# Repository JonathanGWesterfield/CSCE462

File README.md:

# CSCE 462

Repo to store all lab assignments and eventually the project code for this class

# Wiki Page for this repository can be found here:
[AutoSpiel Wiki Page](https://github.com/JonathanGWesterfield/CSCE462/wiki/Project-Outline "AutoSpiel Wiki Page")

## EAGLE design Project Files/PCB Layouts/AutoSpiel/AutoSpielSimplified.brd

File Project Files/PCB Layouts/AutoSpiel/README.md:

# Important Info
* The schematic is called "AutoSpielSimplified.sch" 
    * This was the final attempt
    * WARNING: this schematic was made without looking at the pinout for the Nu32. There were a couple of corrections that had to be made when building the AutoSpiel (jumping wires across the circuit board)
    * It is highly advised to modify the designs in order to match the Nu32 more closely (the 30 pin connectors)
* The final board layout file is called "AutoSpiel v1.2a"
    * The other files are just different versions and attempts
    * This board had a ground plane in order to dissapate heat
    * Was better than having a single ground trace
* CAM jobs must be done using the FEDC guidlines 
    * Instructions can be found in the FEDC Guidelines folder
    * CAM job file can be found in the FEDC Guidelines folder

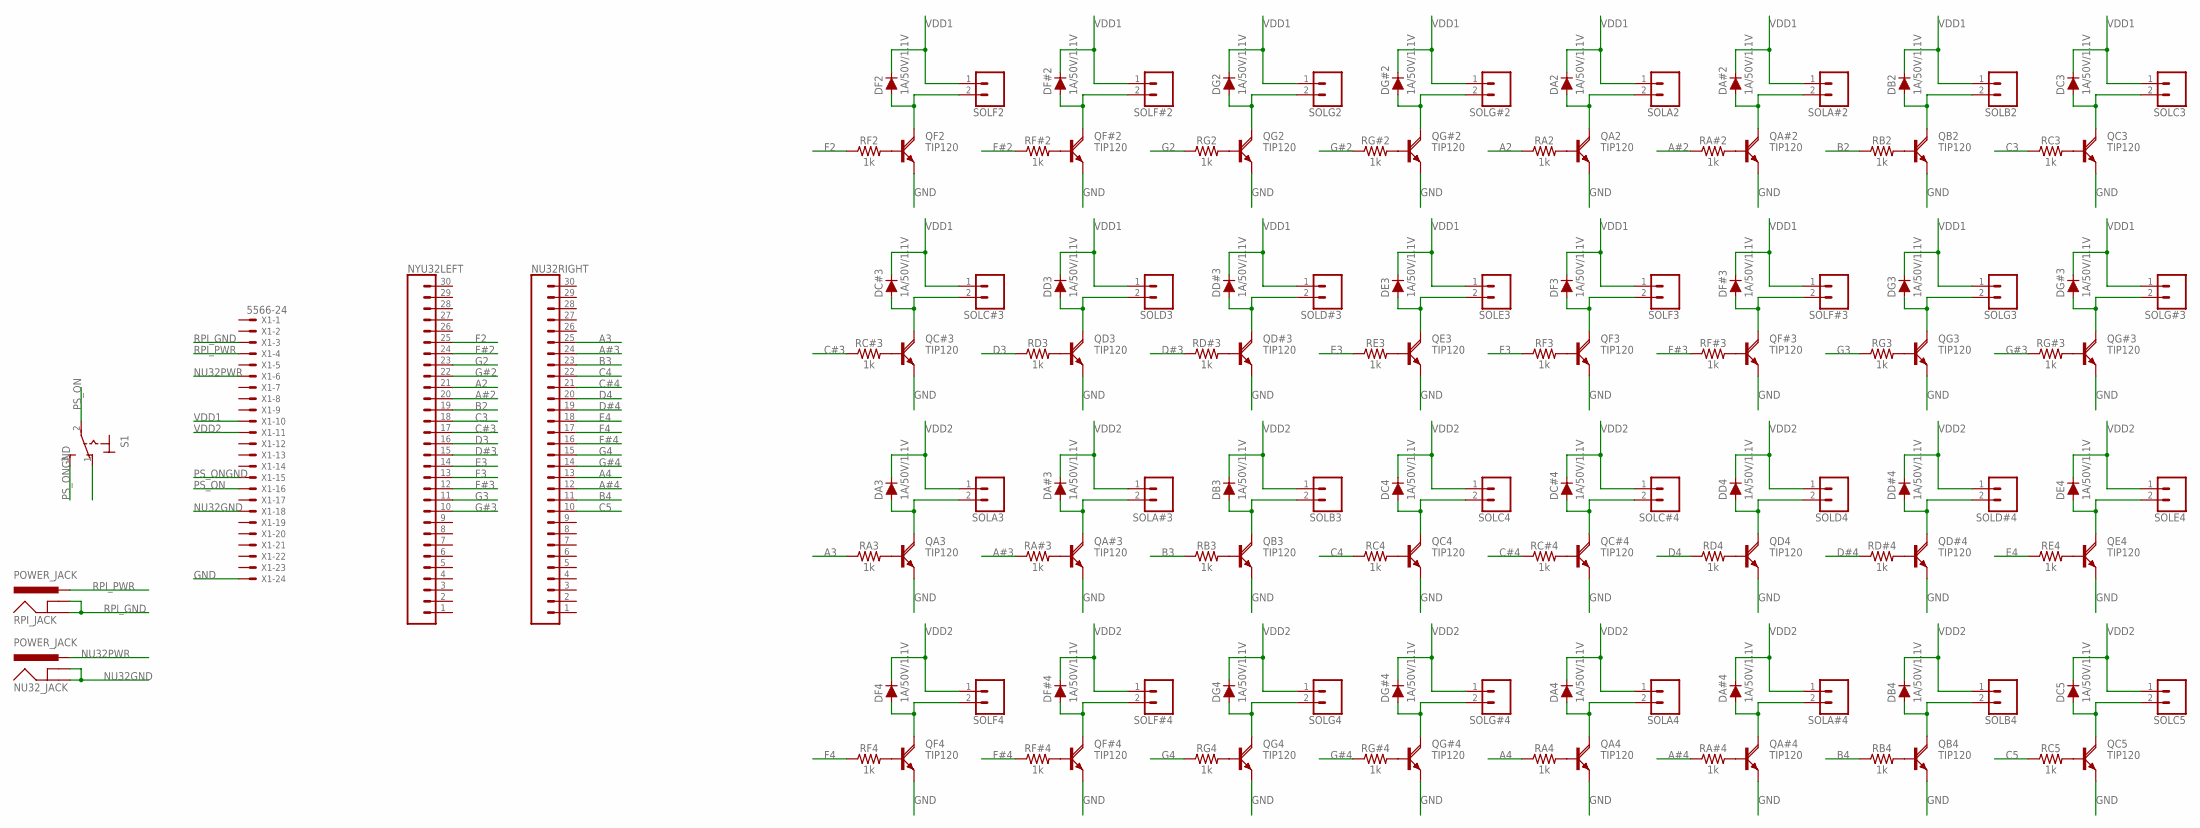
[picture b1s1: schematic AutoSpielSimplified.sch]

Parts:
DA2, DA3, DA4: 1A/50V/1.1V; DIODE-1N4001
DA#2, DA#3, DA#4: 1A/50V/1.1V; DIODE-1N4001
DB2, DB3, DB4: 1A/50V/1.1V; DIODE-1N4001
DC3, DC4, DC5: 1A/50V/1.1V; DIODE-1N4001
DC#3, DC#4: 1A/50V/1.1V; DIODE-1N4001
DD3, DD4: 1A/50V/1.1V; DIODE-1N4001
DD#3, DD#4: 1A/50V/1.1V; DIODE-1N4001
DE3, DE4: 1A/50V/1.1V; DIODE-1N4001
DF2, DF3, DF4: 1A/50V/1.1V; DIODE-1N4001
DF#2, DF#3, DF#4: 1A/50V/1.1V; DIODE-1N4001
DG2, DG3, DG4: 1A/50V/1.1V; DIODE-1N4001
DG#2, DG#3, DG#4: 1A/50V/1.1V; DIODE-1N4001
NU32RIGHT: CONN_30; 1X30
NU32_JACK: POWER_JACK; POWER_JACK_PTH
NYU32LEFT: CONN_30; 1X30
QA2, QA3, QA4: TIP120; TO220AH
QA#2, QA#3, QA#4: TIP120; TO220AH
QB2, QB3, QB4: TIP120; TO220AH
QC3, QC4, QC5: TIP120; TO220AH
QC#3, QC#4: TIP120; TO220AH
QD3, QD4: TIP120; TO220AH
QD#3, QD#4: TIP120; TO220AH
QE3, QE4: TIP120; TO220AH
QF2, QF3, QF4: TIP120; TO220AH
QF#2, QF#3, QF#4: TIP120; TO220AH
QG2, QG3, QG4: TIP120; TO220AH
QG#2, QG#3, QG#4: TIP120; TO220AH
RA2, RA3, RA4: 1k; AXIAL-0.3
RA#2, RA#3, RA#4: 1k; AXIAL-0.3
RB2, RB3, RB4: 1k; AXIAL-0.3
RC3, RC4, RC5: 1k; AXIAL-0.3
RC#3, RC#4: 1k; AXIAL-0.3
RD3, RD4: 1k; AXIAL-0.3
RD#3, RD#4: 1k; AXIAL-0.3
RE3, RE4: 1k; AXIAL-0.3
RF2, RF3, RF4: 1k; AXIAL-0.3
RF#2, RF#3, RF#4: 1k; AXIAL-0.3
RG2, RG3, RG4: 1k; AXIAL-0.3
RG#2, RG#3, RG#4: 1k; AXIAL-0.3
RPI_JACK: POWER_JACK; POWER_JACK_PTH
S1: M9040P
SOLA2, SOLA3, SOLA4: CONN_02PTH4; 1X02_XTRA_BIG
SOLA#2, SOLA#3, SOLA#4: CONN_02PTH4; 1X02_XTRA_BIG
SOLB2, SOLB3, SOLB4: CONN_02PTH4; 1X02_XTRA_BIG
SOLC3, SOLC4, SOLC5: CONN_02PTH4; 1X02_XTRA_BIG
SOLC#3, SOLC#4: CONN_02PTH4; 1X02_XTRA_BIG
SOLD3, SOLD4: CONN_02PTH4; 1X02_XTRA_BIG
SOLD#3, SOLD#4: CONN_02PTH4; 1X02_XTRA_BIG
SOLE3, SOLE4: CONN_02PTH4; 1X02_XTRA_BIG
SOLF2, SOLF3, SOLF4: CONN_02PTH4; 1X02_XTRA_BIG
SOLF#2, SOLF#3, SOLF#4: CONN_02PTH4; 1X02_XTRA_BIG
SOLG2, SOLG3, SOLG4: CONN_02PTH4; 1X02_XTRA_BIG
SOLG#2, SOLG#3, SOLG#4: CONN_02PTH4; 1X02_XTRA_BIG
X1: 5566-24

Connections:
A2: NYU32LEFT.21, RA2.P$1 (1)
A3: NU32RIGHT.25, RA3.P$1 (1)
A4: NU32RIGHT.13, RA4.P$1 (1)
A#2: NYU32LEFT.20, RA#2.P$1 (1)
A#3: NU32RIGHT.24, RA#3.P$1 (1)
A#4: NU32RIGHT.12, RA#4.P$1 (1)
B2: NYU32LEFT.19, RB2.P$1 (1)
B3: NU32RIGHT.23, RB3.P$1 (1)
B4: NU32RIGHT.11, RB4.P$1 (1)
C3: NYU32LEFT.18, RC3.P$1 (1)
C4: NU32RIGHT.22, RC4.P$1 (1)
C5: NU32RIGHT.10, RC5.P$1 (1)
C#3: NYU32LEFT.17, RC#3.P$1 (1)
C#4: NU32RIGHT.21, RC#4.P$1 (1)
D3: NYU32LEFT.16, RD3.P$1 (1)
D4: NU32RIGHT.20, RD4.P$1 (1)
D#3: NYU32LEFT.15, RD#3.P$1 (1)
D#4: NU32RIGHT.19, RD#4.P$1 (1)
E3: NYU32LEFT.14, RE3.P$1 (1)
E4: NU32RIGHT.18, RE4.P$1 (1)
F2: NYU32LEFT.25, RF2.P$1 (1)
F3: NYU32LEFT.13, RF3.P$1 (1)
F4: NU32RIGHT.17, RF4.P$1 (1)
F#2: NYU32LEFT.24, RF#2.P$1 (1)
F#3: NYU32LEFT.12, RF#3.P$1 (1)
F#4: NU32RIGHT.16, RF#4.P$1 (1)
G2: NYU32LEFT.23, RG2.P$1 (1)
G3: NYU32LEFT.11, RG3.P$1 (1)
G4: NU32RIGHT.15, RG4.P$1 (1)
G#2: NYU32LEFT.22, RG#2.P$1 (1)
G#3: NYU32LEFT.10, RG#3.P$1 (1)
G#4: NU32RIGHT.14, RG#4.P$1 (1)
GND: QA2.E, QA3.E, QA4.E, QA#2.E, QA#3.E, QA#4.E, QB2.E, QB3.E, QB4.E, QC3.E, QC4.E, QC5.E, QC#3.E, QC#4.E, QD3.E, QD4.E, QD#3.E, QD#4.E, QE3.E, QE4.E, QF2.E, QF3.E, QF4.E, QF#2.E, QF#3.E, QF#4.E, QG2.E, QG3.E, QG4.E, QG#2.E, QG#3.E, QG#4.E, X1.24
unnamed: QF2.B, RF2.P$2 (2)
unnamed: QC#3.B, RC#3.P$2 (2)
unnamed: DF2.A, QF2.C, SOLF2.2
unnamed: QF#2.B, RF#2.P$2 (2)
unnamed: DF#2.A, QF#2.C, SOLF#2.2
unnamed: DC#3.A, QC#3.C, SOLC#3.2
unnamed: QG2.B, RG2.P$2 (2)
unnamed: DG2.A, QG2.C, SOLG2.2
unnamed: QD3.B, RD3.P$2 (2)
unnamed: QG#2.B, RG#2.P$2 (2)
unnamed: DG#2.A, QG#2.C, SOLG#2.2
unnamed: DD3.A, QD3.C, SOLD3.2
unnamed: QA2.B, RA2.P$2 (2)
unnamed: DA2.A, QA2.C, SOLA2.2
unnamed: QD#3.B, RD#3.P$2 (2)
unnamed: QA#2.B, RA#2.P$2 (2)
unnamed: DA#2.A, QA#2.C, SOLA#2.2
unnamed: DD#3.A, QD#3.C, SOLD#3.2
unnamed: QB2.B, RB2.P$2 (2)
unnamed: DB2.A, QB2.C, SOLB2.2
unnamed: QE3.B, RE3.P$2 (2)
unnamed: QC3.B, RC3.P$2 (2)
unnamed: DC3.A, QC3.C, SOLC3.2
unnamed: DE3.A, QE3.C, SOLE3.2
unnamed: QA3.B, RA3.P$2 (2)
unnamed: DA3.A, QA3.C, SOLA3.2
unnamed: QF3.B, RF3.P$2 (2)
unnamed: DF3.A, QF3.C, SOLF3.2
unnamed: QF#3.B, RF#3.P$2 (2)
unnamed: DF#3.A, QF#3.C, SOLF#3.2
unnamed: QG3.B, RG3.P$2 (2)
unnamed: DG3.A, QG3.C, SOLG3.2
unnamed: QG#3.B, RG#3.P$2 (2)
unnamed: DG#3.A, QG#3.C, SOLG#3.2
unnamed: QF4.B, RF4.P$2 (2)
unnamed: DF4.A, QF4.C, SOLF4.2
unnamed: QF#4.B, RF#4.P$2 (2)
unnamed: DF#4.A, QF#4.C, SOLF#4.2
unnamed: QG4.B, RG4.P$2 (2)
unnamed: DG4.A, QG4.C, SOLG4.2
unnamed: QG#4.B, RG#4.P$2 (2)
unnamed: DG#4.A, QG#4.C, SOLG#4.2
unnamed: QA4.B, RA4.P$2 (2)
unnamed: DA4.A, QA4.C, SOLA4.2
unnamed: QA#4.B, RA#4.P$2 (2)
unnamed: DA#4.A, QA#4.C, SOLA#4.2
unnamed: QB4.B, RB4.P$2 (2)
unnamed: DB4.A, QB4.C, SOLB4.2
unnamed: QC5.B, RC5.P$2 (2)
unnamed: DC5.A, QC5.C, SOLC5.2
unnamed: QA#3.B, RA#3.P$2 (2)
unnamed: DA#3.A, QA#3.C, SOLA#3.2
unnamed: QB3.B, RB3.P$2 (2)
unnamed: DB3.A, QB3.C, SOLB3.2
unnamed: QC4.B, RC4.P$2 (2)
unnamed: DC4.A, QC4.C, SOLC4.2
unnamed: QC#4.B, RC#4.P$2 (2)
unnamed: DC#4.A, QC#4.C, SOLC#4.2
unnamed: QD4.B, RD4.P$2 (2)
unnamed: DD4.A, QD4.C, SOLD4.2
unnamed: QD#4.B, RD#4.P$2 (2)
unnamed: DD#4.A, QD#4.C, SOLD#4.2
unnamed: QE4.B, RE4.P$2 (2)
unnamed: DE4.A, QE4.C, SOLE4.2
NU32GND: NU32_JACK.GND, NU32_JACK.GNDBREAK, X1.18
NU32PWR: NU32_JACK.PWR, X1.6
PS_ON: S1.2, X1.16
PS_ONGND: S1.3 (S), X1.15
RPI_GND: RPI_JACK.GND, RPI_JACK.GNDBREAK, X1.3
RPI_PWR: RPI_JACK.PWR, X1.4
VDD1: DA2.C, DA#2.C, DB2.C, DC3.C, DC#3.C, DD3.C, DD#3.C, DE3.C, DF2.C, DF3.C, DF#2.C, DF#3.C, DG2.C, DG3.C, DG#2.C, DG#3.C, SOLA2.1, SOLA#2.1, SOLB2.1, SOLC3.1, SOLC#3.1, SOLD3.1, SOLD#3.1, SOLE3.1, SOLF2.1, SOLF3.1, SOLF#2.1, SOLF#3.1, SOLG2.1, SOLG3.1, SOLG#2.1, SOLG#3.1, X1.10
VDD2: DA3.C, DA4.C, DA#3.C, DA#4.C, DB3.C, DB4.C, DC4.C, DC5.C, DC#4.C, DD4.C, DD#4.C, DE4.C, DF4.C, DF#4.C, DG4.C, DG#4.C, SOLA3.1, SOLA4.1, SOLA#3.1, SOLA#4.1, SOLB3.1, SOLB4.1, SOLC4.1, SOLC5.1, SOLC#4.1, SOLD4.1, SOLD#4.1, SOLE4.1, SOLF4.1, SOLF#4.1, SOLG4.1, SOLG#4.1, X1.11

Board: 2 copper layers, 134 parts (0 on the bottom side), 105 nets, no tracks yet.

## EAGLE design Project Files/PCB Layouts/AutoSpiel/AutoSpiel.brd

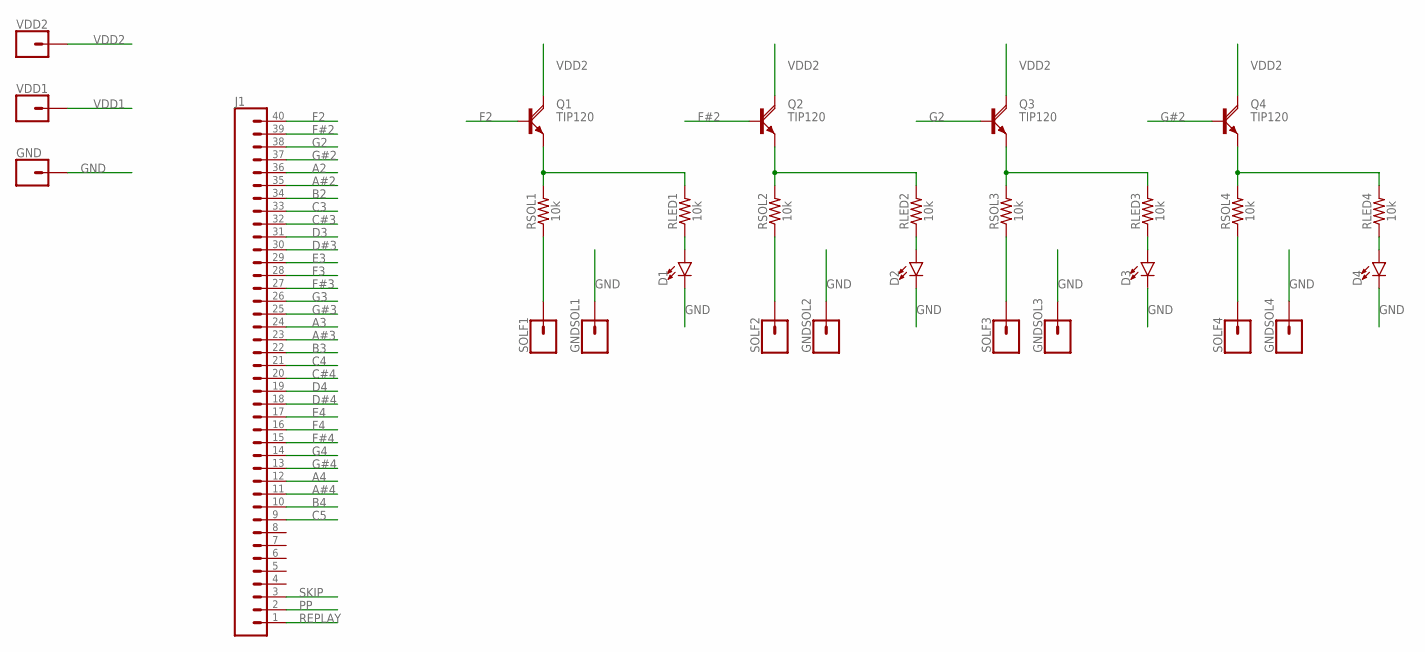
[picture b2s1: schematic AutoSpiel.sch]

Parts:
D1, D2, D3, D4: LED3MM; LED_3MM
GND: CONN_01; 1X01
GNDSOL1, GNDSOL2, GNDSOL3, GNDSOL4: CONN_01; 1X01
J1: CONN_40; 1X40
Q1, Q2, Q3, Q4: TIP120; TO220AH
RLED1, RLED2, RLED3, RLED4: 10k; AXIAL-0.3-KIT
RSOL1, RSOL2, RSOL3, RSOL4: 10k; AXIAL-0.3-KIT
SOLF1, SOLF2, SOLF3, SOLF4: CONN_01; 1X01
VDD1, VDD2: CONN_01; 1X01

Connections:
A2: J1.36
A3: J1.24
A4: J1.12
A#2: J1.35
A#3: J1.23
A#4: J1.11
B2: J1.34
B3: J1.22
B4: J1.10
C3: J1.33
C4: J1.21
C5: J1.9
C#3: J1.32
C#4: J1.20
D3: J1.31
D4: J1.19
D#3: J1.30
D#4: J1.18
E3: J1.29
E4: J1.17
F2: J1.40, Q1.B
F3: J1.28
F4: J1.16
F#2: J1.39, Q2.B
F#3: J1.27
F#4: J1.15
G2: J1.38, Q3.B
G3: J1.26
G4: J1.14
G#2: J1.37, Q4.B
G#3: J1.25
G#4: J1.13
GND: D1.K (C), D2.K (C), D3.K (C), D4.K (C), GND.1, GNDSOL1.1, GNDSOL2.1, GNDSOL3.1, GNDSOL4.1
unnamed: Q2.E, RLED2.P$2 (2), RSOL2.P$2 (2)
unnamed: RSOL2.P$1 (1), SOLF2.1
unnamed: D2.A, RLED2.P$1 (1)
unnamed: Q3.E, RLED3.P$2 (2), RSOL3.P$2 (2)
unnamed: RSOL3.P$1 (1), SOLF3.1
unnamed: Q1.E, RLED1.P$2 (2), RSOL1.P$2 (2)
unnamed: D3.A, RLED3.P$1 (1)
unnamed: Q4.E, RLED4.P$2 (2), RSOL4.P$2 (2)
unnamed: RSOL4.P$1 (1), SOLF4.1
unnamed: D4.A, RLED4.P$1 (1)
unnamed: RSOL1.P$1 (1), SOLF1.1
unnamed: D1.A, RLED1.P$1 (1)
PP: J1.2
REPLAY: J1.1
SKIP: J1.3
VDD1: VDD1.1
VDD2: Q1.C, Q2.C, Q3.C, Q4.C, VDD2.1

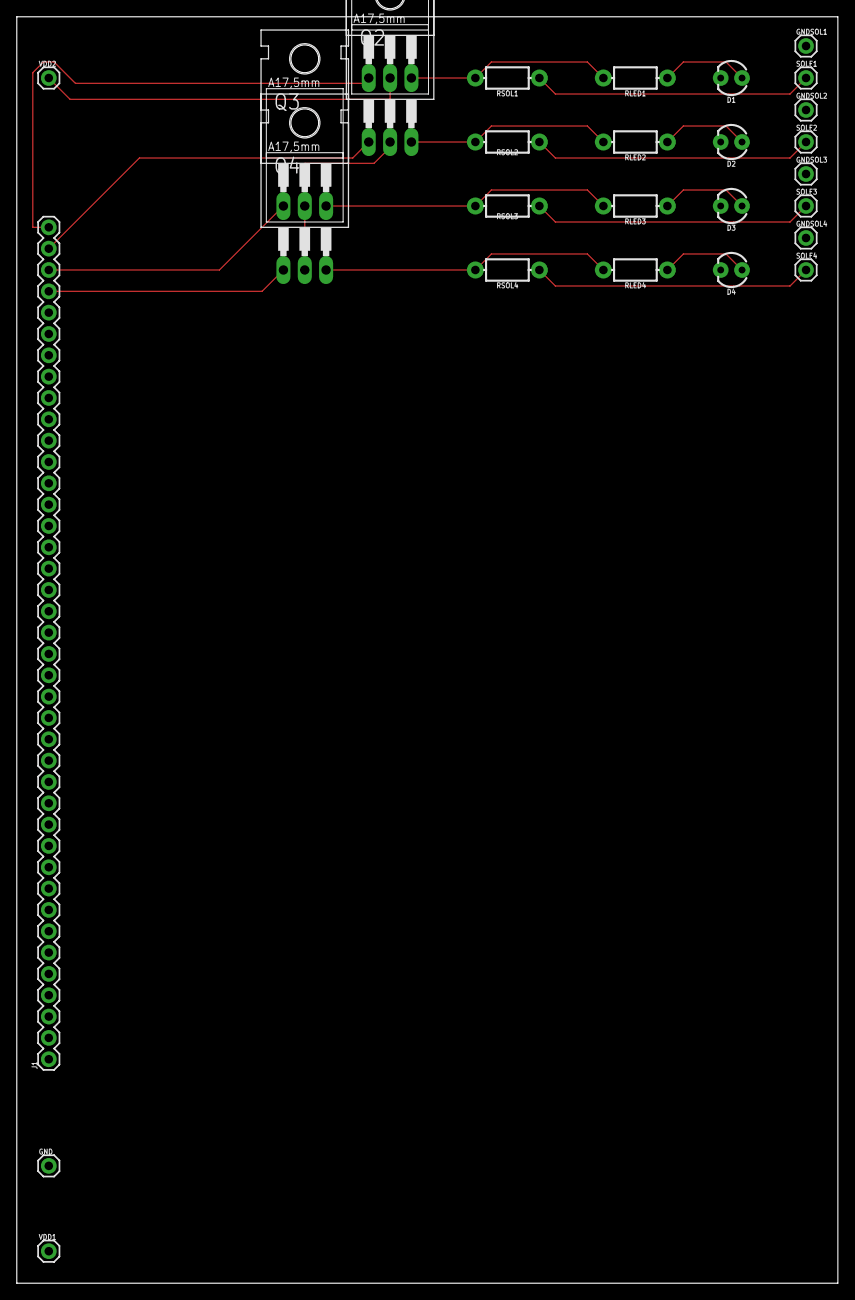
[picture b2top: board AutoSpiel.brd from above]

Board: 2 copper layers, 97.8 x 150.8 mm, 28 parts (0 on the bottom side), 18 nets.

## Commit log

2018-09-23 Added Lab 2 and the lab manuals for the class
2018-09-23 Created Readme
2018-09-25 Added the lab report for lab 2
2018-10-08 Added the cost chart for the piano project
2018-10-08 Updated parts list and added the dummy project folder for lab 4
2018-10-09 Added documentation files for the UBW
2018-10-15 Reorganized files
2018-10-16 Changed up the .gitignore file to add more functionality. Added the tone.js library to the repo
2018-10-16 Added the transistors data sheet and created a folder for the Serial Communication development between the RPi and UBW32
2018-10-16 Added link to the wiki page
2018-10-16 Added some sample midi files
2018-10-16 Update the .gitignore file for MSOffice and added to the project proposal
2018-10-16 Added more to Project Proposal
2018-10-17 Finished Project Proposal
2018-10-17 Added files for lab 5
2018-10-18 fixed the frequency function in lab5 oscilloscope.py
2018-10-18 Updated the project proposal
2018-10-18 Cleaned up project proposal
2018-10-18 Added initial PCB files
2018-10-19 Added more to the board to do fit testing
2018-10-23 Added converted midi files (in json format)
2018-10-24 Added a couple of helpful pictures and redid the circuit based off of stuff I've researched
2018-10-25 Added a second schematic for a simplfied solenoid circuit (vs the one with a capacitor and PNP transistor in it)
2018-10-26 Updated the simplified schematic
2018-10-29 Added some reference C documention for the UBW (specifically the pic32 chip)
2018-10-29 Added a textbook on programming the PIC32
2018-10-30 Reorganized folder structure for the microcontroller stuff and added a new textbook for the PIC32
2018-10-30 Added updated schematic for the autospiel
2018-10-30 Finished schematic. Started board layout
2018-10-30 Created 2 versions of the finished board
2018-10-31 Labeled everything on the board layout
2018-10-31 Added labels on the board
2018-10-31 Added the rules for pcb printing at Tamu FEDC
2018-10-31 Created a board with the tamu FEDC DRC file
2018-11-03 Made 3 different versions of the pcb
2018-11-04 Added pinout of control board
2018-11-05 Finished and finalized Autospiel v1.3a. Created gerber files but need to confirm they are correct
2018-11-06 Added updated FEDC files. Created new output gerber files for pcb fab
2018-11-27 Add files via upload
    Sample working program without serial communication
2018-11-27 Silent Night midi
2018-11-28 Added all order reciepts and blacked out my address
2018-12-03 Added some pictures
2018-12-03 Added the board schematics and layout as images
2018-12-03 Converted CR2 Images to png's
2018-12-03 Added git lfs
2018-12-03 Added Team Picture
2018-12-03 Added the picture of the final product
2018-12-03 info.txt
2018-12-03 FINAL RPi FILES!!!
2018-12-04 Removed unnecessary folders and moved files around
2018-12-04 Added Readmes to the PCB Layouts folder
2018-12-04 Moved the README for the PCB Layouts folder
2018-12-04 Updated .gitattributes to use git lfs
2018-12-04 Added compressed project photos

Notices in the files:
parts and their libraries:
SparkFun-LED: Licensing: Creative Commons ShareAlike 4.0 International - https://creativecommons.org/licenses/by-sa/4.0
